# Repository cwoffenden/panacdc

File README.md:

Panasonic CX-DP60 Emulator
==========================

The project is a combination of hardware and software to emulate a Panasonic CX-DP60 CD Changer (CDC), allowing early 1990s car radios to use the CD inputs as an auxilary. Tested with a Panasonic CQ-LR2450A (from an MG RV8) but should work with others from the same era.

Without a CDC connected the radio ignores changing to the CD input, hence the need to emulate its presence. This isn't a new idea; others have created emulators for newer CDCs (see [CDCEmu](http://q1.se/cdcemu/), [VAG CDC Faker](http://dev.shyd.de/2013/09/avr-raspberry-pi-vw-beta-vag-cdc-faker/), etc.) but these don't work with older radios.

I started by looking at the [DP60's schematics](https://raw.githubusercontent.com/cwoffenden/panacdc/master/doc/schematic.pdf) (actually, I started with CDCEmu, which didn't work, so I rolled up my sleeves and did this) and recording the traffic with a [Saleae Logic](https://www.saleae.com/). The radio's remote commands look to be using a variant of the [NEC protocol](https://www.vishay.com/docs/80071/dataform.pdf) whereas the CDC's data is a byte orientated synchronous serial stream:

A close-up of the CDC's serial data can bee seen [here](https://raw.githubusercontent.com/cwoffenden/panacdc/master/doc/logic-2.png), with a [Logic](https://www.saleae.com/downloads) capture of the traffic between the CDC and radio [here](https://github.com/cwoffenden/panacdc/raw/master/doc/cd-radio-off.logicdata) (note that the Logic hardware isn't required to view the capture).

It's not necessary to understand or fully decode the communication, just to recognise and replay. The documented source and schematic are available above, but for anyone wishing to simply build it, it's enough to order a PCB (either from the [Eagle](http://www.cadsoftusa.com/) [project files](https://github.com/cwoffenden/panacdc/tree/master/pcb), the resulting [Gerbers](https://github.com/cwoffenden/panacdc/raw/master/out/board.zip), or direct from [OSH Park](https://oshpark.com/shared_projects/Xu28lOTu)) and program the flash (via the ISP connector on the board using the [prebuilt firmware](https://github.com/cwoffenden/panacdc/blob/master/out/flash.elf) and [any](https://www.amazon.co.uk/dp/B00AVRHVPO) [low-cost](https://www.sparkfun.com/categories/7) [programmer](https://www.arduino.cc/en/Tutorial/ArduinoISP)). It was designed to be built with nothing more than a regular soldering iron.

Parts can be ordered from [Farnell](http://www.farnell.com/), [Mouser](http://www.mouser.com/) or any other componment supplier (the BOM is available [here](https://github.com/cwoffenden/panacdc/blob/master/out/parts.csv), which can be sent directly to Farnell's [BOM upload](http://uk.farnell.com/help-parts-list-bom-upload)). The finished project has a USB connector to power a Bluetooth or DLNA receiver (tested with an [Arcam miniBlink](http://www.arcam.co.uk/mini.htm)). A [conformal coating](https://raw.githubusercontent.com/cwoffenden/panacdc/master/doc/board.jpeg) was added to protect the board from any moisture.

How Does It Work?
-----------------

When powered on the board sends `0x73FFFFFFFFFF7F7B` every 40ms to the radio (on the _data_, _clock_ and _strobe_ lines; see [sendBytes()](https://github.com/cwoffenden/panacdc/blob/master/src/main.c#L177)) to say there is a CDC connected. When the radio switches to the CD input, with either a `0x08` or `0xA4` command (see [ISR(INT0_vect)](https://github.com/cwoffenden/panacdc/blob/master/src/main.c#L272)) the board then starts sending `0x33FFCF81CF7F7F3B`, meaning the first CD is playing track one (it probably contains time data and so on, but it's not necessary to know, just to replay what was captured). The only other radio command understood is `0x10`, sent when switching back to the tuner or cassette, or when powering off, to which the response is `0x13FFFFFFFFFF7F1B` (without which it's not possible to turn the radio off).

Output from the emulator to the radio is [bit banged](https://en.wikipedia.org/wiki/Bit_banging), with timing close enough to the DP60 that the radio is happy (but simplified; the real timing is much more complex, just not required). Input to the emulator from the radio uses a hardware interrupt (`INT0`) and one of the hardware timers (`TIMER1`) to decode the _remocon_ signal.

Improvements
------------

Send delays would be better implemented using the ATtiny's other hardware timer, then the board could drop into low-power mode (not really needed but is the _correct_ way of doing things). Multiple audio sources could be supported by changing virtual CDs (with the circuit extended so the ATtiny switches analogue sources).

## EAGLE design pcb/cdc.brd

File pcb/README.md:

Schematic and board layout for [CadSoft Eagle](http://www.cadsoftusa.com/). The project file is for 6.5 but should work in newer versions.

### Note
The 8-pin DIN used isn't the exact type found on the DP60 (and therefore the original cabling). The DP60 has pins arranged in a U-shape (262 degrees) whereas the socket used is C-shaped (270 degrees). It's close and with a little force the cable can be made to fit. Sourcing a PCB mount U-shaped socket no longer seems possible (removing one fitted to a broken DP60 is an option, though the PCB would need altering accordingly).

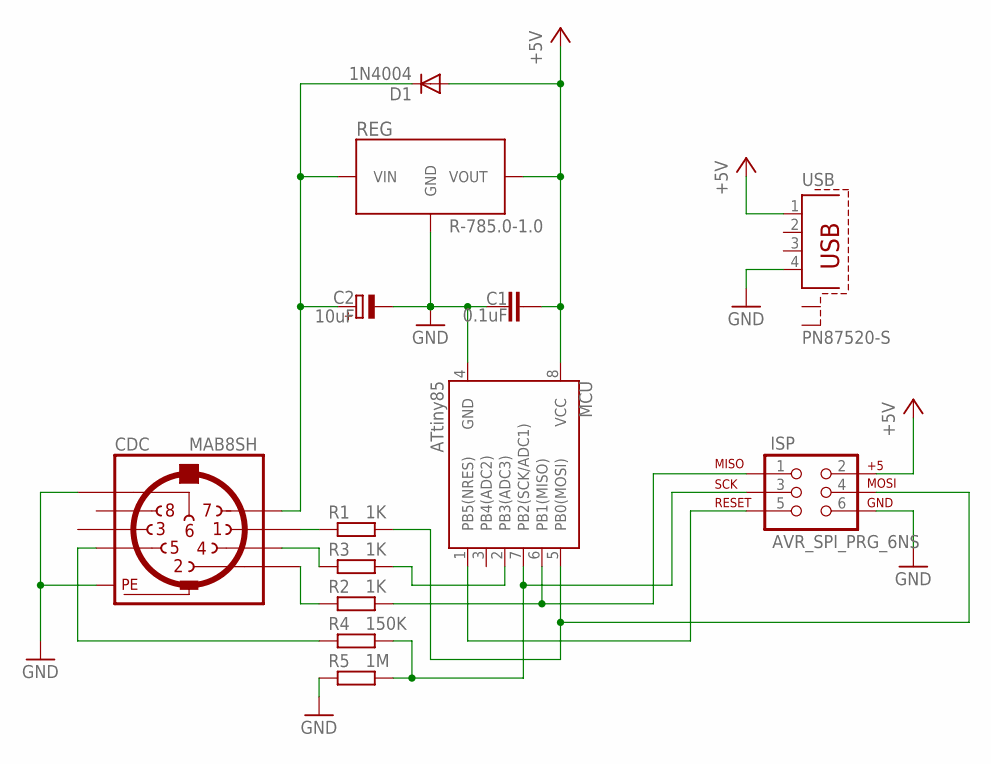
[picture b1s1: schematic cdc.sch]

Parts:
C1: 0.1uF; C5B3
C2: 10uF; E1,8-4
CDC: MAB8SH
D1: 1N4004; DO41-10
ISP: AVR_SPI_PRG_6NS; 2X3-NS
MCU: ATtiny85; DIP08
R1, R2, R3: 1K; 0207/7
R4: 150K; 0207/7
R5: 1M; 0207/7
REG: VREG-RECOM-785.0-1.0
USB: PN87520-S

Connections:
+5V: C1.2, D1.A, ISP.2, MCU.8 (VCC), REG.VOUT, USB.1
GND: C1.1, C2.-, CDC.6, CDC.PE, CDC.PE@ (PE), ISP.6, MCU.4 (GND), R5.1, REG.GND, USB.4
unnamed: C2.+, CDC.7, D1.C, REG.VIN
unnamed: ISP.4, MCU.5 (PB0(MOSI)), R1.2
unnamed: ISP.1, MCU.6 (PB1(MISO)), R2.2
unnamed: MCU.2 (PB3(ADC3)), R3.2
unnamed: ISP.5, MCU.1 (PB5(NRES))
unnamed: ISP.3, MCU.7 (PB2(SCK/ADC1)), R4.2, R5.2
unnamed: CDC.2, R2.1
unnamed: CDC.4, R3.1
unnamed: CDC.1, R1.1
unnamed: CDC.5, R4.1

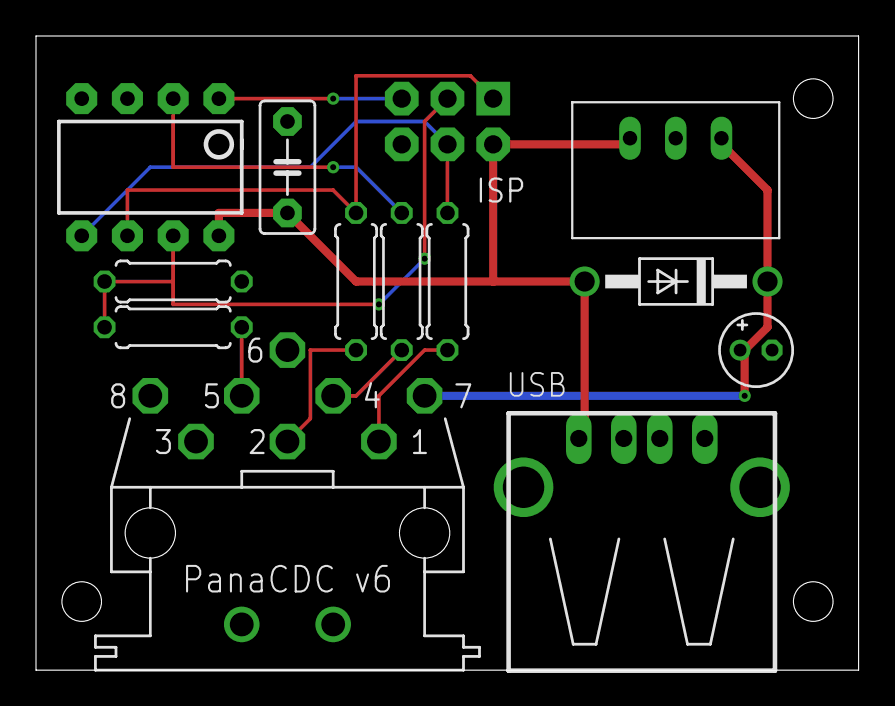
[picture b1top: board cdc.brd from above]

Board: 2 copper layers, 45.7 x 35.2 mm, 13 parts (0 on the bottom side), 12 nets.

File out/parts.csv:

Part,Value,Farnell
C1,0.1uF,1216445
C2,10uF,1902051
CDC,MAB8SH,809913
D1,1N4004,9565027
ISP,AVR_SPI_PRG_6NS,1593440
MCU,ATtiny85,1455162
R1,1K,9342400
R2,1K,9342400
R3,1K,9342400
R4,150K,9342648
R5,1M,9342435
REG,VREG-RECOM-785.0-1.0,1793142
USB,PN87520-S,2112381

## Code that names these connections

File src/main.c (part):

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 * \def CDC_DAT
 * 8-pin DIN pin 1 (\e data from CDC).
 */
#define CDC_DAT PB0
/**
 * \def CDC_CLK
 * 8-pin DIN pin 2 (\e clock from CDC).
 */
#define CDC_CLK PB1
/**
 * \def CDC_STB
 * 8-pin DIN pin 4 (\e strobe from CDC).
 */
#define CDC_STB PB3
/**
 * \def REMOCON
 * 8-pin DIN pin 5 (\e remocon from radio).
 */
#define REMOCON PB2

//***************************************************************************/

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
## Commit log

2016-05-02 Initial commit
    Initial board and firmware commit.
2016-05-08 Accounted for different MCU timings
    Testing on a different ATtiny85 showed huge timing differences for the
    timer, so the timings were relaxed further.
2016-05-08 Added images
    Added photos and write-up images.
2016-05-09 Removed superfluous file
2016-05-09 Added BOM
2016-05-09 Added Logic capture
2016-05-09 Initial write-up
2016-05-09 Minor tweaks
2016-05-09 Updated docs
    Added schematic, updated docs.
2016-05-09 Added Farnell BOM upload link
2016-05-09 Extended the description
2016-05-09 Minor tidy
2016-05-09 Display tab size
2016-05-09 Expanded on the Logic capture
2016-05-10 Minor docs
2016-05-11 Minor typo
2016-05-11 Minor docs clarification
2016-05-11 Minor clarification
2016-05-15 Added note on socket choice
2016-05-16 Further clarification on the DIN connector
2017-08-30 Minor tidy.
2017-10-16 Deleted superfluous file.
2019-09-28 Minor: add license
2025-12-16 Spelling

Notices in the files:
parts and their libraries:
SparkFun-DigitalIC: Licensing: Creative Commons ShareAlike 4.0 International - https://creativecommons.org/licenses/by-sa/4.0
